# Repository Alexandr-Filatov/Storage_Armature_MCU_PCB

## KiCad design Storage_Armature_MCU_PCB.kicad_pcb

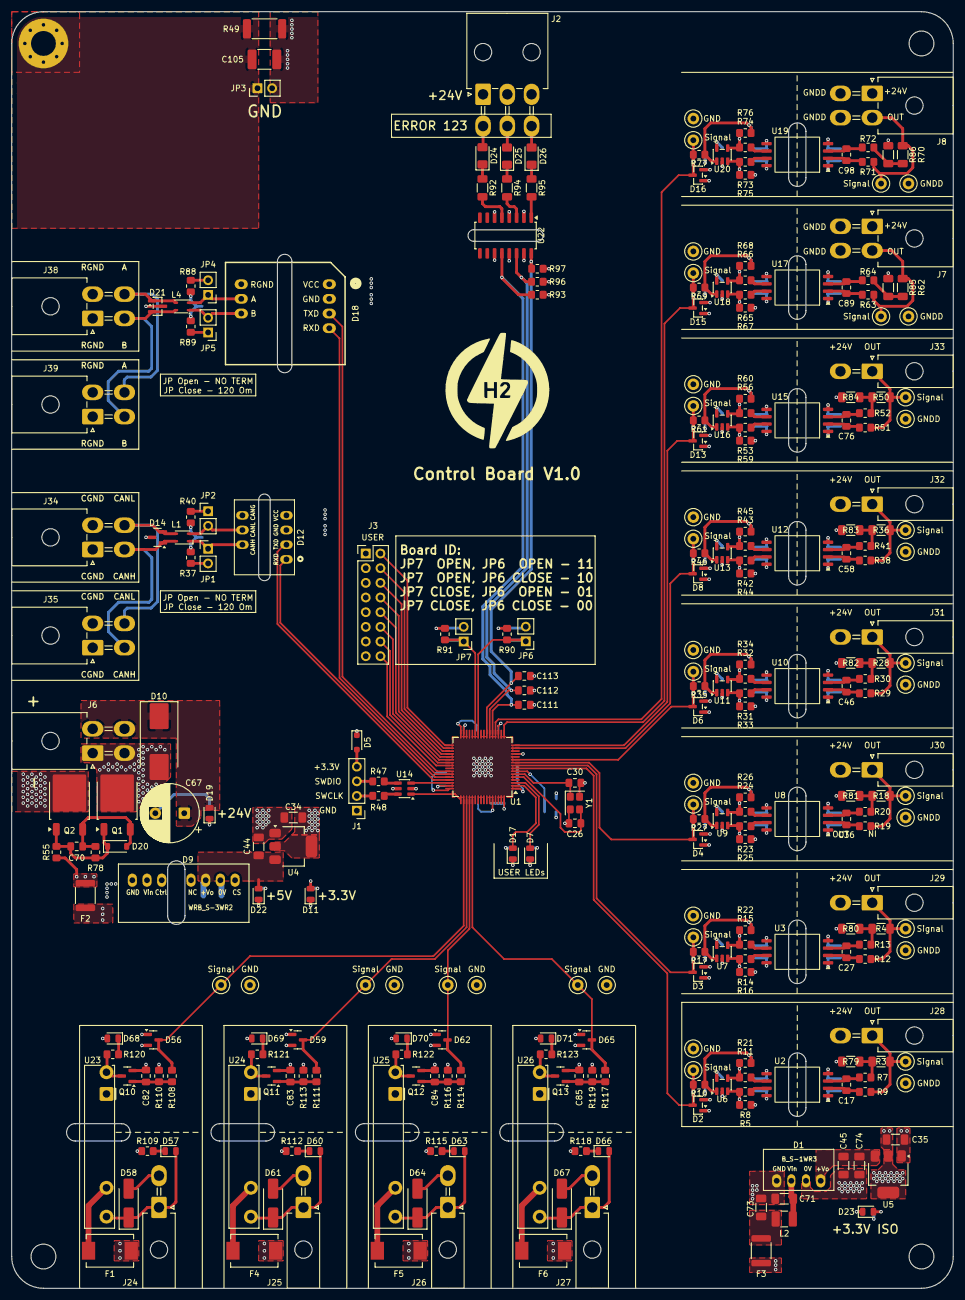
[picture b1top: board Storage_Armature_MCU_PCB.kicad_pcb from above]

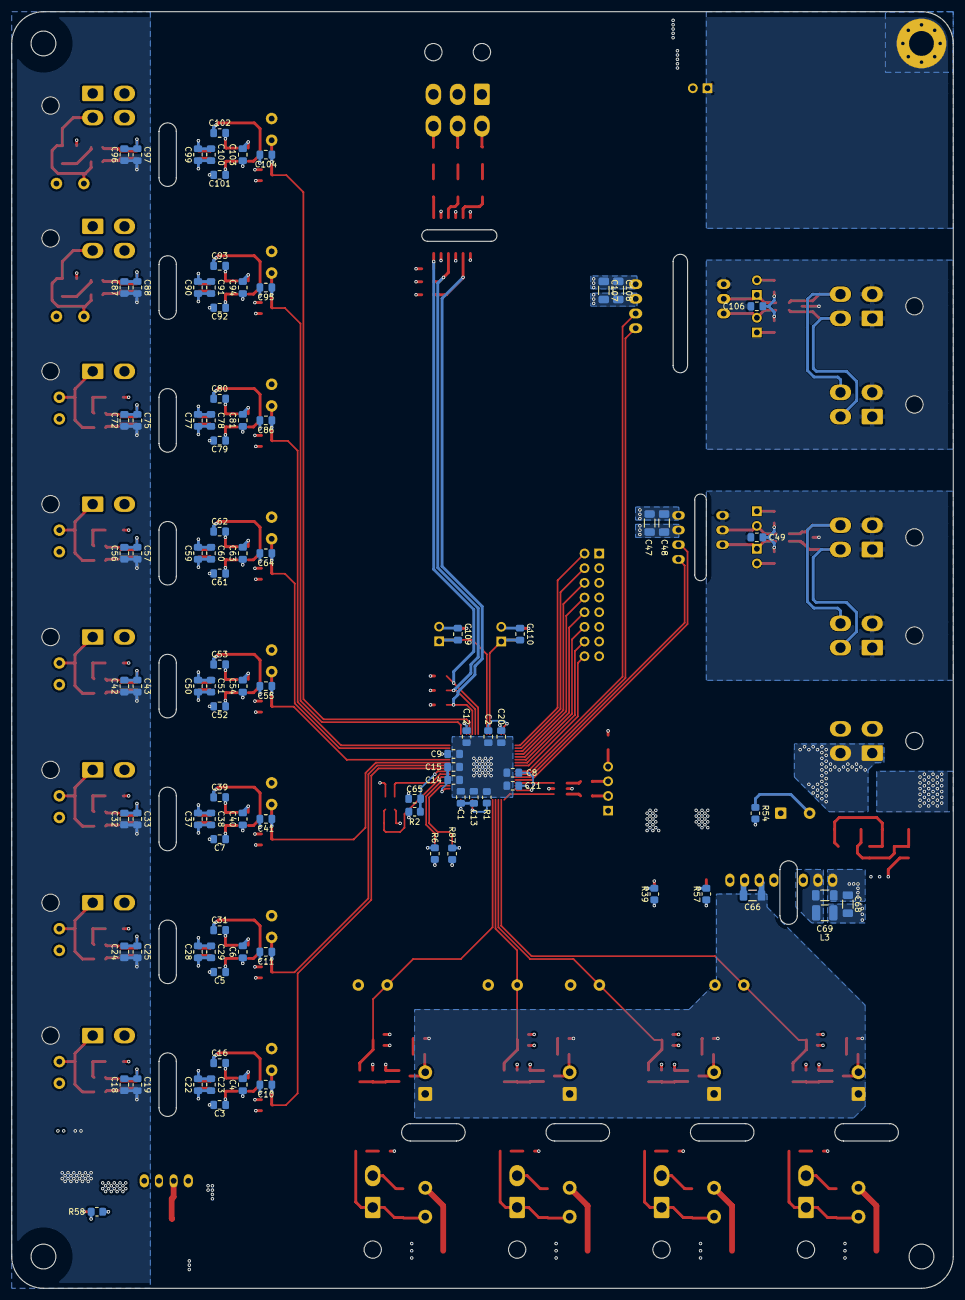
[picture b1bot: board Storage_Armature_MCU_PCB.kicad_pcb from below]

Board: 4 copper layers, 163.0 x 221.0 mm, 381 parts (95 on the bottom side), 186 nets.

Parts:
C1, C2, C4, C6, C8, C9, C12, C13, C19, C22, C25, C28, C33, C37, C40, C43, C50, C54, C57, C59, C63, C65, C70, C75, C77, C81, C88, C90, C94, C97, C99, C103, C109, C110, C111, C112, C113: 100n; C_0805_2012Metric_Pad1.18x1.45mm_HandSolder
C3, C5, C7, C16, C31, C39, C49, C52, C53, C61, C62, C79, C80, C82, C83, C84, C85, C92, C93, C101, C102, C106: 10n; C_0805_2012Metric_Pad1.18x1.45mm_HandSolder
C10, C11, C41, C55, C64, C86, C95, C104: 56p; C_0805_2012Metric_Pad1.18x1.45mm_HandSolder
C14: 4.7u; C_0805_2012Metric_Pad1.18x1.45mm_HandSolder
C15: 1u; C_0805_2012Metric_Pad1.18x1.45mm_HandSolder
C17, C27, C36, C46, C58, C76, C89, C98: 22n; C_0805_2012Metric_Pad1.18x1.45mm_HandSolder
C18, C20, C21, C23, C24, C29, C32, C38, C42, C51, C56, C60, C72, C78, C87, C91, C96, C100: 2.2u; C_0805_2012Metric_Pad1.18x1.45mm_HandSolder
C26, C30: 12p; C_0805_2012Metric_Pad1.18x1.45mm_HandSolder
C34, C35, C44, C45, C47, C66, C74, C107: 10u; C_1206_3216Metric_Pad1.33x1.80mm_HandSolder
C48, C108: 100n; C_1206_3216Metric_Pad1.33x1.80mm_HandSolder
C67: 330u; CP_Radial_D10.0mm_P5.00mm
C68, C69, C71, C73: 4.7u; C_1206_3216Metric_Pad1.33x1.80mm_HandSolder
C105: 2.2n; C_1812_4532Metric_Pad1.57x3.40mm_HandSolder
D1: B_S-1WR3
D2, D3, D4, D6, D8, D13, D14, D15, D16, D21, D56, D59, D62, D65: SOT-23
D5: D_SOD-323_HandSoldering
D7, D11, D17, D19, D22, D23, D57, D60, D63, D66, D68, D69, D70, D71: LED_0805_2012Metric
D9: WRB_S-3WR2
D10: D_SMC_Handsoldering
D12: TD5(3)01MCANFD
D18: TD301D485H-AB
D20: D_SOD-123
D24, D25, D26: LED_1206_3216Metric_Pad1.42x1.75mm_HandSolder
D58, D61, D64, D67: D_SMA_Handsoldering
F1, F4, F5, F6: Fuse_Bourns_MF-SM_7.98x5.44mm
F2, F3: Fuse_1812_4532Metric
H2: MountingHole_Pad; MountingHole_4.3mm_M4_Pad_Via
H3, H4, H5: MountingHole; MountingHole_4.3mm_M4
J1: PinHeader_1x04_P2.54mm_Vertical
J2: Molex_Mini-Fit_Jr_5569-06A2_2x03_P4.20mm_Horizontal
J3: PinHeader_2x08_P2.54mm_Vertical
J6, J7, J8, J34, J35, J38, J39: Molex_Mini-Fit_Jr_5569-04A2_2x02_P4.20mm_Horizontal
J24, J25, J26, J27, J28, J29, J30, J31, J32, J33: Molex_Mini-Fit_Jr_5569-02A2_2x01_P4.20mm_Horizontal
JP1, JP2, JP3, JP4, JP5, JP6, JP7: PinHeader_1x02_P2.54mm_Vertical
L1, L4: L_CommonModeChoke_TDK_ACM2520-2P
L2, L3: 6.8u; L_1210_3225Metric_Pad1.42x2.65mm_HandSolder
Q1, Q2: TO-252-2
Q10, Q11, Q12, Q13: SOT-23
R1, R2, R8, R11, R14, R15, R23, R24, R31, R32, R42, R43, R53, R56, R65, R66, R73, R74, R90, R91, R93, R96, R97, R110, R113, R116, R119: 10k; R_0805_2012Metric_Pad1.20x1.40mm_HandSolder
R3, R4, R18, R28, R36, R50, R62, R70: 10; R_1206_3216Metric_Pad1.30x1.75mm_HandSolder
R5, R16, R21, R22, R25, R26, R33, R34, R44, R45, R59, R60, R67, R68, R75, R76: 20k; R_0805_2012Metric_Pad1.20x1.40mm_HandSolder
R6, R39, R57, R58, R87, R108, R111, R114, R117, R120, R121, R122, R123: 1k; R_0805_2012Metric_Pad1.20x1.40mm_HandSolder
R7, R9, R12, R13, R19, R20, R29, R30, R38, R41, R51, R52, R63, R64, R71, R72: 100; R_0805_2012Metric_Pad1.20x1.40mm_HandSolder
R10, R17, R27, R35, R46, R61, R69, R77: 120; R_0805_2012Metric_Pad1.20x1.40mm_HandSolder
R37, R40, R88, R89: 59; R_0805_2012Metric_Pad1.20x1.40mm_HandSolder
R47, R48: 20; R_0805_2012Metric_Pad1.20x1.40mm_HandSolder
R49: 1M; R_2512_6332Metric_Pad1.40x3.35mm_HandSolder
R54, R109, R112, R115, R118: 4.7k; R_0805_2012Metric_Pad1.20x1.40mm_HandSolder
R55: 100k; R_0805_2012Metric_Pad1.20x1.40mm_HandSolder
R78: 470k; R_0805_2012Metric_Pad1.20x1.40mm_HandSolder
R79, R80, R81, R82, R83, R84, R85, R86: 0; R_1206_3216Metric_Pad1.30x1.75mm_HandSolder
R92, R94, R95: 3.3k; R_1206_3216Metric_Pad1.30x1.75mm_HandSolder
TP1, TP2, TP3, TP4, TP5, TP6, TP7, TP8, TP9, TP10, TP11, TP12, TP13, TP14, TP15, TP16, TP17, TP18, TP19, TP20, TP21, TP22, TP23, TP24, TP25, TP26, TP27, TP28, TP29, TP30, TP31, TP32, TP36, TP37, TP38, TP39, TP40, TP41, TP42, TP43: TestPoint; TestPoint_Loop_D1.80mm_Drill1.0mm_Beaded
U1: LQFP-64_10x10mm_P0.5mm
U2, U3, U8, U10, U12, U15, U17, U19: SOIC-8_7.5x5.85mm_P1.27mm
U4, U5: SOT-223-3_TabPin2
U6, U7, U9, U11, U13, U16, U18, U20: SOT-23-5
U14: SOT-23-6
U22: SOP-16_4.4x10.4mm_P1.27mm
U23, U24, U25, U26: Finder_34.81
Y1: 16M; Crystal_SMD_SeikoEpson_FA238-4Pin_3.2x2.5mm

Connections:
+3.3V: C1.1, C2.1, C4.1, C6.1, C8.1, C9.1, C12.1, C13.1, C14.1, C15.1, C22.1, C23.1, C28.1, C29.1, C34.2, C37.1, C38.1, C40.1, C47.1, C48.1, C50.1, C51.1, C54.1, C59.1, C60.1, C63.1, C77.1, C78.1, C81.1, C90.1, C91.1, C94.1, C99.1, C100.1, C103.1, C107.1, C108.1, D2.2 (K), D3.2 (K), D4.2 (K), D5.1 (K), D6.2 (K), D8.2 (K), D11.2 (A), D12.4 (VCC), D13.2 (K), D15.2 (K), D16.2 (K), D18.1 (VCC), D56.2 (K), D59.2 (K), D62.2 (K), D65.2 (K), R2.1, R90.1, R91.1, R93.2, R96.2, R97.2, U1.1 (VBAT), U1.13 (VDDA), U1.19 (VDD), U1.32 (VDD), U1.48 (VDD), U1.64 (VDD), U2.8 (V+), U3.8 (V+), U4.2 (VO), U6.5 (V+), U7.5 (V+), U8.8 (V+), U9.5 (V+), U10.8 (V+), U11.5 (V+), U12.8 (V+), U13.5 (V+), U14.5 (VBUS), U15.8 (V+), U16.5 (V+), U17.8 (V+), U18.5 (V+), U19.8 (V+), U20.5 (V+)
+3.3V_ISO: C18.1, C19.1, C24.1, C25.1, C32.1, C33.1, C35.2, C42.1, C43.1, C56.1, C57.1, C72.1, C75.1, C87.1, C88.1, C96.1, C97.1, D23.2 (A), U2.1 (V+), U3.1 (V+), U5.2 (VO), U8.1 (V+), U10.1 (V+), U12.1 (V+), U15.1 (V+), U17.1 (V+), U19.1 (V+)
+5V: C44.2, C66.1, D9.6 (+Vo), D22.2 (A), D68.2 (A), D69.2 (A), D70.2 (A), D71.2 (A), U4.3 (VI), U23.A1, U24.A1, U25.A1, U26.A1
+24V: C67.1, D10.1 (A1), D19.2 (A), F1.2, F2.1, F3.1, F4.2, F5.2, F6.2, J2.1, J2.2, J2.3, J6.2, J6.4, J7.1, J8.1, J28.2, J29.2, J30.2, J31.2, J32.2, J33.2, R55.2
-24V_IN: D10.2 (A2), J6.1, J6.3, Q1.2 (D)
/A: D21.1 (K), J38.4, J39.4, L4.3
/B: D21.2 (K), J38.3, J39.3, L4.4
/CANH: D14.1 (K), J34.3, J35.3, L1.4
/CANL: D14.2 (K), J34.4, J35.4, L1.3
/CAN_RXD_MCU: D12.1 (RXD), U1.44 (PA11)
/CAN_TXD_MCU: D12.2 (TXD), U1.45 (PA12)
/ERROR_LvL1: C111.1, R93.1, U1.21 (PA5), U22.12
/ERROR_LvL1_IN: D24.2 (A), J2.4
/ERROR_LvL2: C112.1, R96.1, U1.22 (PA6), U22.14
/ERROR_LvL2_IN: D25.2 (A), J2.5
/ERROR_LvL3: C113.1, R97.1, U1.23 (PA7), U22.16
/ERROR_LvL3_IN: D26.2 (A), J2.6
/GPIO1: J3.2, U1.33 (PB12)
/GPIO2: J3.4, U1.34 (PB13)
/GPIO3: J3.6, U1.35 (PB14)
/GPIO4: J3.8, U1.36 (PB15)
/GPIO5: J3.10, U1.37 (PC6)
/GPIO6: J3.12, U1.38 (PC7)
/GPIO7: J3.14, U1.39 (PC8)
/GPIO8: J3.16, U1.40 (PC9)
/RS_RXD_MCU: D18.4 (RXD), U1.43 (PA10)
/RS_TXD_MCU: D18.3 (TXD), U1.42 (PA9)
/SWCLK: U1.49 (PA14), U14.1 (I/O1)
/SWDIO: U1.46 (PA13), U14.3 (I/O2)
/Sensor_1/P_measure_MCU: C10.1, D2.3 (common), R10.2, TP1.1 (1_1), U1.8 (PC0)
/Sensor_2/P_measure_MCU: C11.1, D3.3 (common), R17.2, TP2.1 (1_1), U1.9 (PC1)
/Sensor_3/P_measure_MCU: C41.1, D4.3 (common), R27.2, TP3.1 (1_1), U1.10 (PC2)
/Sensor_4/P_measure_MCU: C55.1, D6.3 (common), R35.2, TP4.1 (1_1), U1.11 (PC3)
/Sensor_5/P_measure_MCU: C64.1, D8.3 (common), R46.2, TP5.1 (1_1), U1.15 (PA1)
/Sensor_6/P_measure_MCU: C86.1, D13.3 (common), R61.2, TP6.1 (1_1), U1.16 (PA2)
/Sensor_flow_1/F_measure_MCU: C95.1, D15.3 (common), R69.2, TP7.1 (1_1), U1.17 (PA3)
/Sensor_flow_2/F_measure_MCU: C104.1, D16.3 (common), R77.2, TP8.1 (1_1), U1.20 (PA4)
/Solenoid1_MCU: D56.3 (common), R108.1, TP40.1 (1_1), U1.50 (PA15)
/Solenoid2_MCU: D59.3 (common), R111.1, TP41.1 (1_1), U1.51 (PC10)
/Solenoid3_MCU: D62.3 (common), R114.1, TP42.1 (1_1), U1.52 (PC11)
/Solenoid4_MCU: D65.3 (common), R117.1, TP43.1 (1_1), U1.53 (PC12)
BOOT0: R1.2, U1.60 (BOOT0)
GND: C1.2, C2.2, C3.1, C4.2, C5.1, C6.2, C7.1, C8.2, C9.2, C10.2, C11.2, C12.2, C13.2, C14.2, C15.2, C20.2, C21.2, C22.2, C23.2, C26.1, C28.2, C29.2, C30.2, C34.1, C37.2, C38.2, C40.2, C41.2, C44.1, C47.2, C48.2, C50.2, C51.2, C52.1, C54.2, C55.2, C59.2, C60.2, C61.1, C63.2, C64.2, C65.1, C66.2, C77.2, C78.2, C79.1, C81.2, C82.2, C83.2, C84.2, C85.2, C86.2, C90.2, C91.2, C92.1, C94.2, C95.2, C99.2, C100.2, C101.1, C103.2, C104.2, C105.2, C107.2, C108.2, C109.2, C110.2, C111.2, C112.2, C113.2, D2.1 (A), D3.1 (A), D4.1 (A), D6.1 (A), D8.1 (A), D9.7 (0V), D12.3 (GND), D13.1 (A), D15.1 (A), D16.1 (A), D18.2 (GND), D56.1 (A), D59.1 (A), D62.1 (A), D65.1 (A), J1.1, J3.1, J3.3, J3.5, J3.7, J3.9, J3.11, J3.13, J3.15, JP3.2 (B), JP6.2 (B), JP7.2 (B), Q10.2 (S), Q11.2 (S), Q12.2 (S), Q13.2 (S), R1.1, R5.1, R6.2, R16.1, R25.1, R33.1, R39.2, R44.1, R49.2, R57.2, R59.1, R67.1, R75.1, R87.2, R110.1, R113.1, R116.1, R119.1, TP9.1 (1_1), TP10.1 (1_1), TP11.1 (1_1), TP12.1 (1_1), TP13.1 (1_1), TP14.1 (1_1), TP15.1 (1_1), TP16.1 (1_1), TP36.1 (1_1), TP37.1 (1_1), TP38.1 (1_1), TP39.1 (1_1), U1.12 (VSSA), U1.18 (VSS), U1.63 (VSS), U2.5 (V-), U3.5 (V-), U4.1 (GND), U6.2 (V-), U7.2 (V-), U8.5 (V-), U9.2 (V-), U10.5 (V-), U11.2 (V-), U12.5 (V-), U13.2 (V-), U14.2 (GND), U15.5 (V-), U16.2 (V-), U17.5 (V-), U18.2 (V-), U19.5 (V-), U20.2 (V-), U22.11, U22.13, U22.15, Y1.2, Y1.4
GNDD: C18.2, C19.2, C24.2, C25.2, C32.2, C33.2, C35.1, C42.2, C43.2, C45.1, C56.2, C57.2, C67.2, C68.2, C69.2, C71.2, C72.2, C73.2, C74.2, C75.2, C87.2, C88.2, C96.2, C97.2, D1.1 (GND), D1.3 (0V), D9.1 (GND), D58.2 (A), D61.2 (A), D64.2 (A), D67.2 (A), J7.3, J7.4, J8.3, J8.4, J24.2, J25.2, J26.2, J27.2, Q2.2 (D), R54.2, R58.2, R79.2, R80.2, R81.2, R82.2, R83.2, R84.2, R85.2, R86.2, R109.2, R112.2, R115.2, R118.2, TP25.1 (1_1), TP26.1 (1_1), TP27.1 (1_1), TP28.1 (1_1), TP29.1 (1_1), TP30.1 (1_1), TP31.1 (1_1), TP32.1 (1_1), U2.4 (V-), U3.4 (V-), U5.1 (GND), U8.4 (V-), U10.4 (V-), U12.4 (V-), U15.4 (V-), U17.4 (V-), U19.4 (V-), U22.2, U22.4, U22.6
GND_CAN: C49.2, D12.5 (CANG), D14.3 (A), J34.1, J34.2, J35.1, J35.2
GND_RS485: C106.2, D18.10 (RGND), D21.3 (A), J38.1, J38.2, J39.1, J39.2
NRST: C65.2, R2.2, U1.7 (NRST)
unnamed: C16.2, R10.1, R21.2, U6.1
unnamed: C17.1, R9.2, U2.2 (+)
unnamed: C17.2, R7.2, U2.3 (-)
unnamed: C27.1, R12.2, U3.2 (+)
unnamed: C27.2, R13.2, U3.3 (-)
unnamed: C31.2, R17.1, R22.2, U7.1
unnamed: C36.1, R19.2, U8.2 (+)
unnamed: C36.2, R20.2, U8.3 (-)
unnamed: C39.2, R26.2, R27.1, U9.1
unnamed: C46.1, R29.2, U10.2 (+)
unnamed: C46.2, R30.2, U10.3 (-)
unnamed: C49.1, R37.1, R40.2
unnamed: C53.2, R34.2, R35.1, U11.1
unnamed: C58.1, R38.2, U12.2 (+)
unnamed: C58.2, R41.2, U12.3 (-)
unnamed: C62.2, R45.2, R46.1, U13.1
unnamed: C68.1, F2.2, L3.1
unnamed: C73.1, F3.2, L2.1
unnamed: C76.1, R51.2, U15.2 (+)
unnamed: C76.2, R52.2, U15.3 (-)
unnamed: C80.2, R60.2, R61.1, U16.1
unnamed: C89.1, R63.2, U17.2 (+)
unnamed: C89.2, R64.2, U17.3 (-)
unnamed: C93.2, R68.2, R69.1, U18.1
unnamed: C98.1, R71.2, U19.2 (+)
unnamed: C98.2, R72.2, U19.3 (-)
unnamed: C102.2, R76.2, R77.1, U20.1
unnamed: C106.1, R88.1, R89.2
unnamed: C45.2, C74.1, D1.4 (+Vo), U5.3 (VI)
unnamed: C71.1, D1.2 (Vin), L2.2
unnamed: D5.2 (A), J1.4
unnamed: D7.2 (A), U1.3 (PC14)
unnamed: D7.1 (K), R6.1
unnamed: C69.1, D9.2 (Vin), L3.2
unnamed: D11.1 (K), R39.1
unnamed: D12.7 (CANH), JP1.1 (A), L1.1
unnamed: D12.6 (CANL), JP2.2 (B), L1.2
unnamed: D17.2 (A), U1.2 (PC13)
unnamed: D17.1 (K), R87.1
unnamed: D18.9 (A), JP4.1 (A), L4.2
unnamed: D18.8 (B), JP5.2 (B), L4.1
unnamed: D19.1 (K), R54.1
unnamed: C70.2, D20.2 (A), Q1.3 (S), Q2.3 (S), R78.2
unnamed: C70.1, D20.1 (K), Q1.1 (G), Q2.1 (G), R55.1, R78.1
unnamed: D22.1 (K), R57.1
unnamed: D23.1 (K), R58.1
unnamed: D24.1 (K), R92.1
unnamed: D25.1 (K), R94.1
unnamed: D26.1 (K), R95.1
unnamed: D57.2 (A), D58.1 (K), J24.1, U23.14
unnamed: D57.1 (K), R109.1
unnamed: D60.2 (A), D61.1 (K), J25.1, U24.14
unnamed: D60.1 (K), R112.1
unnamed: D63.2 (A), D64.1 (K), J26.1, U25.14
unnamed: D63.1 (K), R115.1
unnamed: D66.2 (A), D67.1 (K), J27.1, U26.14
unnamed: D66.1 (K), R118.1
unnamed: D68.1 (K), R120.1
unnamed: D69.1 (K), R121.1
unnamed: D70.1 (K), R122.1
unnamed: D71.1 (K), R123.1
unnamed: F1.1, U23.11
unnamed: F4.1, U24.11
unnamed: F5.1, U25.11
unnamed: F6.1, U26.11
unnamed: J1.2, R48.2
unnamed: J1.3, R47.2
unnamed: J7.2, R62.1, R63.1, TP23.1 (1_1)
unnamed: J8.2, R70.1, R71.1, TP24.1 (1_1)
unnamed: J28.1, R3.1, R9.1, TP17.1 (1_1)
unnamed: J29.1, R4.1, R12.1, TP18.1 (1_1)
unnamed: J30.1, R18.1, R19.1, TP19.1 (1_1)
unnamed: J31.1, R28.1, R29.1, TP20.1 (1_1)
unnamed: J32.1, R36.1, R38.1, TP21.1 (1_1)
unnamed: J33.1, R50.1, R51.1, TP22.1 (1_1)
unnamed: JP1.2 (B), R37.2
unnamed: JP2.1 (A), R40.1
unnamed: C105.1, H2.1 (1_1), JP3.1 (A), R49.1
unnamed: JP4.2 (B), R88.2
unnamed: JP5.1 (A), R89.1
unnamed: C109.1, JP6.1 (A), R90.2, U1.26 (PB0)
unnamed: C110.1, JP7.1 (A), R91.2, U1.27 (PB1)
unnamed: Q10.3 (D), R120.2, U23.A2
unnamed: C82.1, Q10.1 (G), R108.2, R110.2
unnamed: Q11.3 (D), R121.2, U24.A2
unnamed: C83.1, Q11.1 (G), R111.2, R113.2
unnamed: Q12.3 (D), R122.2, U25.A2
unnamed: C84.1, Q12.1 (G), R114.2, R116.2
unnamed: Q13.3 (D), R123.2, U26.A2
unnamed: C85.1, Q13.1 (G), R117.2, R119.2
unnamed: R3.2, R7.1, R79.1
unnamed: R8.1, U2.7 (+)
unnamed: R11.1, U2.6 (-)
unnamed: R4.2, R13.1, R80.1
unnamed: R14.1, U3.7 (+)
unnamed: R15.1, U3.6 (-)
unnamed: R18.2, R20.1, R81.1
unnamed: R23.1, U8.7 (+)
unnamed: R24.1, U8.6 (-)
unnamed: R28.2, R30.1, R82.1
unnamed: R31.1, U10.7 (+)
unnamed: R32.1, U10.6 (-)
unnamed: R36.2, R41.1, R83.1
unnamed: R42.1, U12.7 (+)
unnamed: R43.1, U12.6 (-)
unnamed: R47.1, U14.4 (I/O2)
unnamed: R48.1, U14.6 (I/O1)
unnamed: R50.2, R52.1, R84.1
unnamed: R53.1, U15.7 (+)
unnamed: R56.1, U15.6 (-)
unnamed: R62.2, R64.1, R85.1
unnamed: R65.1, U17.7 (+)
unnamed: R66.1, U17.6 (-)
unnamed: R70.2, R72.1, R86.1
unnamed: R73.1, U19.7 (+)
unnamed: R74.1, U19.6 (-)
unnamed: R92.2, U22.5
unnamed: R94.2, U22.3
unnamed: R95.2, U22.1
unnamed: C26.2, U1.5 (PH0), Y1.3
unnamed: C30.1, U1.6 (PH1), Y1.1
unnamed: C20.1, U1.31 (VCAP_1)
unnamed: C21.1, U1.47 (VCAP_2)
unnamed: C3.2, R5.2, R8.2, U6.3 (+)
unnamed: C16.1, R11.2, R21.1, U6.4 (-)
unnamed: C5.2, R14.2, R16.2, U7.3 (+)
unnamed: C31.1, R15.2, R22.1, U7.4 (-)
unnamed: C7.2, R23.2, R25.2, U9.3 (+)
unnamed: C39.1, R24.2, R26.1, U9.4 (-)
unnamed: C52.2, R31.2, R33.2, U11.3 (+)
unnamed: C53.1, R32.2, R34.1, U11.4 (-)
unnamed: C61.2, R42.2, R44.2, U13.3 (+)
unnamed: C62.1, R43.2, R45.1, U13.4 (-)
unnamed: C79.2, R53.2, R59.2, U16.3 (+)
unnamed: C80.1, R56.2, R60.1, U16.4 (-)
unnamed: C92.2, R65.2, R67.2, U18.3 (+)
unnamed: C93.1, R66.2, R68.1, U18.4 (-)
unnamed: C101.2, R73.2, R75.2, U20.3 (+)
unnamed: C102.1, R74.2, R76.1, U20.4 (-)

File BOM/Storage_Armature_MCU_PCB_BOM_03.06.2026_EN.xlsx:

Reference | Value | Product Name | Replacement | Package | Description | Quantity | DNP
C1, C2, C4, C6, C8, C9, C12, C13, C19, C22, C25, C28, C33, C37, C40, C43, C50, 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 | 100n |  |  | SMD 0805 | Capacitor SMD 50V | 37
C48, C108 | 100n |  |  | SMD 1206 | Capacitor SMD 50V | 2
C3, C5, C7, C16, C31, C39, C49, C52, C53, C61, C62, C79, C80, C82, C83, C84, C8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 | 10n |  |  | SMD 0805 | Capacitor SMD 50V | 22
C34, C35, C44, C45, C47, C66, C74, C107 | 10u |  |  | SMD 1206 | Capacitor SMD 50V | 8
C26, C30 | 12p |  |  | SMD 0805 | Capacitor SMD 50V | 2
C15 | 1u |  |  | SMD 0805 | Capacitor SMD 50V | 1
C105 | 2.2n |  |  | SMD 1812 | Capacitor SMD 50V | 1
C18, C20, C21, C23, C24, C29, C32, C38, C42, C51, C56, C60, C72, C78, C87, C91,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 | 2.2u |  |  | SMD 0805 | Capacitor SMD 50V | 18
C17, C27, C36, C46, C58, C76, C89, C98 | 22n |  |  | SMD 0805 | Capacitor SMD 50V | 8
C67 | 330u | EEUFR1H331L |  | CP Radial D10.0mm P5.00mm | Polarized capacitor | 1
C14 | 4.7u |  |  | SMD 0805 | Capacitor SMD 50V | 1
C68, C69, C71, C73 | 4.7u |  |  | SMD 1206 | Capacitor SMD 50V | 4
C10, C11, C41, C55, C64, C86, C95, C104 | 56p |  |  | SMD 0805 | Capacitor SMD 50V | 8
D1 | ~ | B2405S-1WR3 |  | S-1WR3 | DC/DC | 1
D58, D61, D64, D67 | ~ | RS1B |  | SMA | Fast recovery diode | 4
D10 | ~ | SMCJ33A |  | SMC | Supressor | 1
D7, D17 | ~ | FYLS-0603UBC |  | SMD 0805 | Blue LED | 2
D11, D19, D22, D23, D57, D60, D63, D66, D68, D69, D70, D71 | ~ | FYLS-0805UYC |  | SMD 0805 | Yellow LED | 12
D24, D25, D26 | ~ | FYLS-0603UBC |  | SMD 1206 | Blue LED | 3
D20 | ~ | BZT52C10 |  | SOD-123 | Zener_Diode | 1
D5 | ~ | LBAT54HT1G |  | SOD-323 | Diode | 1
D14 | ~ | SM24CANB-02HTG |  | SOT-23 | Dual Line CAN Bus Protector, 24Vrwm | 1
D21 | ~ | SM712 |  | SOT-23 | ESD Diode | 1
D2, D3, D4, D6, D8, D13, D15, D16, D56, D59, D62, D65 | ~ | BAT54S |  | SOT-23 | Schottky barrier diode | 12
D18 | ~ | TD301D485H-A |  | TD301D485H-AB | RS485 Transciever | 1
D12 | ~ | TD301MCANFD |  | TD5(3)01MCANFD | CAN Transceiver | 1
D9 | ~ | WRB2403S-3WR2 |  | WRB S-3WR2 | DC/DC | 1
F1, F4, F5, F6 | ~ | MF-SM075/60-2 |  | Fuse Bourns MF-SM 7.98x5.44mm | Fuse SMD | 4
F3 | ~ | MF-MSMF020 |  | SMD 1812 | Fuse SMD | 1
F2 | ~ | MF-MSMF050/30X-2 |  | SMD 1812 | Fuse SMD | 1
J24, J25, J26, J27, J28, J29, J30, J31, J32, J33, J36, J37 | ~ | DS1073-01-2x1MR2T6 |  | Molex Mini-Fit Jr 5569-02A2 2x01 P4.20mm | Connector | 12
J6, J34, J35, J38, J39 | ~ | DS1073-01-2x2MR3T6 |  | Molex Mini-Fit Jr 5569-04A2 2x02 P4.20mm | Connector | 5
J2 | ~ | DS1073-01-2x3MR2T6 |  | Molex Mini-Fit Jr 5569-06A2 2x03 P4.20mm | Connector | 1
J1 | ~ | KLS1-207-1-04-S | DS-1021-1x4 | PinHeader 1x04 P2.54mm | Connector | 1
J3 | ~ | KLS1-207-2-16-S |  | PinHeader 2x08 P2.54mm | Connector | 1
JP1, JP2, JP3, JP4, JP5, JP6, JP7 | ~ | DS1027-2ABN0 |  | PinHeader 1x02 P2.54mm | Jumper | 7
L2, L3 | 6.8u | LQH32CN6R8M53L |  | SMD 1210 | Inductor SMD | 2
L1, L4 | ~ | ACM2520-301-2P-T002 |  | CommonModeChoke TDK ACM2520-2P | Inductor SMD | 2
Q10, Q11, Q12, Q13 | ~ | 2N7002 |  | SOT-23 | N_channel MOSFET | 4
Q1, Q2 | ~ | 20N06 |  | TO-252-2 | N_channel MOSFET | 2
R79, R80, R81, R82, R83, R84, R85, R86 | 0 |  |  | SMD 1206 | Resistor SMD | 8
R57, R58 | 1.1k |  |  | SMD 0805 | Resistor SMD | 2
R3, R4, R18, R28, R36, R50, R62, R70 | 10 |  |  | SMD 1206 | Resistor SMD | 8
R7, R9, R12, R13, R19, R20, R29, R30, R38, R41, R51, R52, R63, R64, R71, R72 | 100 |  |  | SMD 0805 | Resistor SMD | 16
R55 | 100k |  |  | SMD 0805 | Resistor SMD | 1
R1, R2, R8, R11, R14, R15, R23, R24, R31, R32, R42, R43, R53, R56, R65, R66, R7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 | 10k |  |  | SMD 0805 | Resistor SMD | 27
R10, R17, R27, R35, R46, R61, R69, R77 | 120 |  |  | SMD 0805 | Resistor SMD | 8
R49 | 1M |  |  | SMD 2512 | Resistor SMD | 1
R6, R87, R108, R111, R114, R117, R120, R121, R122, R123 | 1k |  |  | SMD 0805 | Resistor SMD | 10
R47, R48 | 20 |  |  | SMD 0805 | Resistor SMD | 2
R5, R16, R21, R22, R25, R26, R33, R34, R44, R45, R59, R60, R67, R68, R75, R76 | 20k |  |  | SMD 0805 | Resistor SMD | 16
R92, R94, R95 | 3.3k |  |  | SMD 1206 | Resistor SMD | 3
R54, R109, R112, R115, R118 | 4.7k |  |  | SMD 0805 | Resistor SMD | 5
R78 | 470k |  |  | SMD 0805 | Resistor SMD | 1
R37, R40, R88, R89 | 59 |  |  | SMD 0805 | Resistor SMD | 4
R39 | 750 |  |  | SMD 0805 | Resistor SMD | 1
U23, U24, U25, U26 | ~ | RSCD06D3 |  | Finder 34.81 | Relay | 4
U1 | ~ | APM32F405RGT6 |  | LQFP-64 10x10mm P0.5mm | MCU | 1
U2, U3, U8, U10, U12, U15, U17, U19 | ~ | NSI1200 |  | SOIC-8 7.5x5.85mm P1.27mm | Digital Isolator | 8
U22 | ~ | LTV-247 |  | SOP-16 4.4x10.4mm P1.27mm | Photocoupler | 1
U4, U5 | ~ | ADP3338AKCZ-3.3RL7 |  | SOT-223-3 | Linear Regulator | 2
U6, U7, U9, U11, U13, U16, U18, U20 | ~ | OPA333 |  | SOT-23-5 | Op-Amp | 8
U14 | ~ | USBLC6-2P6 |  | SOT-23-6 | ESD protection | 1
Y1 | 16M | X322516MOB4SI |  | Crystal SMD SeikoEpson FA238-4Pin 3.2x2.5mm | Crystal | 1

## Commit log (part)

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2026-04-29 zero commit
2026-05-04 VER1.0: сделал все питание и один измерительный канал
2026-05-05 VER1.0: разместил все компоненты
2026-05-05 VER1.0: развел все кроме ножек МК
2026-05-05 VER1.0: добавил предохранители каждому клапану и отдельно по питанию
2026-05-06 VER1.0: объединил земли датчиков и 24В
2026-05-07 VER1.0: добавил светодиоды, тестпоинты и мягкий старт 24В
2026-05-08 VER1.0: добавил RS485, Board ID, вырезы в плате
2026-05-25 VER1.0: добавил сухие контакты и логотип
2026-05-28 VER1.0: добавил схему в PDF
2026-06-01 VER1.0: добавил светодиоды аварии и гребенку для анализатора
2026-06-03 VER1.0: изменил структуру проекта, добавил gitignore, проверил плату на ошибки
2026-06-03 VER1.0: добавил BOM и гербера
2026-06-08 VER1.0: исправил каналы расходомеров, добавил папку с отчетным КД
2026-06-08 VER1.0: обновил гербера
